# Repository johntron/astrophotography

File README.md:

# Astrophotography image processing

## Curriculum

* [Introduction to astrophotography](#introduction-to-astrophotography)
* [Image acquisition](#image-acquisition)
* [Image calibration](#image-calibration)
* [Image stacking](#image-stacking)
* [Image enhancement](#image-enhancement)
* [Color processing](#color-processing)
* [Advanced techniques](#advanced-techniques)
* [Image analysis](#image-analysis)

## Introduction to astrophotography

Learn the basics of astrophotography, including the equipment used, camera settings, and exposure times.

## Image acquisition

Learn how to capture images of the night sky using a digital camera or a telescope.

## Image calibration

Learn how to process raw astronomical images, including dark frame subtraction, flat field correction, and bias
correction.

### 1. Introduction to image calibration

Learn the importance of image calibration in astrophotography and its impact on the final image quality.

<dl>
   <dt>Bias frames</dt>
   <dd>Used to capture electronic bias inherent in sensor (zero point), so it can be removed from light frames. Does not capture or account for read noise.</dd>

   <dt>Dark frames</dt>
   <dd>Used to capture noise caused by heat generated during exposures and amplifiers (dark current), so it can be removed from light frames. Includes electronic bias, so bias frames must be subtracted from dark frames, or only dark frames should be used (no bias frames) - <em>❓ is this true❓</em></dd>

   <dt>Flat frames</dt>
   <dd>Used to capture optical imperfections in imaging path, so it can be corrected for. Can correct for minor vignette, sensor mottling (if any), as well as dust and other stray particles. Captured when all pixels are irradiated the same amount. During image processing, light frames are divided by flat frames. This effectively normalizes the range of each pixel by reducing the brightness of pixels with few optical obstructions.</dd>

   <dt>Flat dark frames</dt>
   <dd>Alternative to bias and dark frames for sensors that can't capture these types of calibration frames effectively.</dd>
</dl>

Reference:

* https://telescope.live/blog/learning-about-amp-glow#:~:text=Amplifier%20glow%20refers%20to%20a,circuitry%20of%20the%20imaging%20chip.

### 2. Capturing calibration frames

Dark and flat frames should be captured using same exposure as light frames. Dust can accumulate on the sensor during imaging, and jostling the instrument can dislodge dist. For these reasons, flat frames should be taken immediately after capturing light frames. Bias frames - if used - should be taken with minimal exposure.

### 2. Dark frame subtraction

Dark bias correction (includes sensor bias):

```python
dark_corrected_image = raw_image - reference_dark_image
```

Reference:

* https://prancer.physics.louisville.edu/astrowiki/index.php/Image_processing_with_Python_and_SciPy#Correcting_and_Combining_Images

### 3. Flat field correction

Flat field correction:

```python
final_image = dark_corrected_image / reference_flat_image
```

Reference:

* https://www.macobservatory.com/blog/2018/11/3/how-to-take-easy-flats-using-an-inexpensive-light-source
* https://prancer.physics.louisville.edu/astrowiki/index.php/Image_processing_with_Python_and_SciPy#Correcting_and_Combining_Images
* https://homepages.inf.ed.ac.uk/rbf/HIPR2/pixdiv.htm

### 4. Bias correction

This isn't necessary when using dark frames, because dark frames include electronic bias; however, if bias frames were used, the correction would use subtraction.

### 6. Image calibration techniques

Individual calibration frames can be combined to create a "master" calibration frame - e.g. master dark frame. These master frames should be combined with light frames of the same exposure.

To save time, a library of calibration frames can be created ahead of time. This avoids the time-consuming process of creating calibration frames during an imaging session. Most (all?) calibration frames can be created while the sun is up; however, accounting for temperature would be hard.

### 7. Image calibration settings

Learn how to adjust image calibration settings to produce the best final image, including choosing the right number of
images to use and the best calibration technique.

### 8. Outstanding questions

* If creating a calibration frame library, how do you account for temperature?
* How many calibration frames should be included in a master frame?

## Image stacking

Learn how to combine multiple images to increase the signal-to-noise ratio and produce a final image
with greater detail.

1. Introduction to image stacking: Learn the basics of image stacking and its importance in astrophotography.
1. Image acquisition: Learn how to capture images of the night sky using a digital camera or a telescope.
1. Image calibration: Learn how to process raw astronomical images, including dark frame subtraction, flat field
   correction, and bias correction.
1. Registration: Learn how to align and register multiple images to be stacked, including techniques for eliminating
   field rotation, field curvature, and focal plane distortion.
2. Methods: Learn about different image stacking methods, including average stacking, median stacking, and sigma
   clipping.
3. Settings: Learn how to adjust image stacking settings to produce the best final image, including choosing the
   right number of images to stack and the best stacking method.
4. Post-processing: Learn how to post-process the final stacked image using techniques such as histogram stretching,
   noise reduction, and sharpening.

## Image enhancement

Learn how to process and enhance final images using techniques such as histogram stretching, noise
reduction, and sharpening.

1. Introduction to image enhancement: Learn the importance of image enhancement in astrophotography and its impact
   on the final image quality.
2. Image processing software: Learn how to use image processing software, such as Adobe Photoshop, GIMP, or
   PixInsight, to enhance astrophotographic images.
2. Histogram stretching: Learn how to adjust the image brightness and contrast using histogram stretching to bring
   out faint details in the image.
2. Noise reduction: Learn how to reduce the noise in an image using techniques such as wavelet processing, selective
   smoothing, and median filtering.
2. Sharpening: Learn how to sharpen the details in an image using techniques such as unsharp masking, high-pass
   filtering, and deconvolution.
2. Color processing: Learn how to adjust the colors in an image to bring out the best representation of the night
   sky, including techniques for color balancing, color correction, and color grading.
2. Layer masks: Learn how to use layer masks to selectively apply image processing techniques to specific areas of
   an image.

## Color processing

Learn how to create a color image from a set of monochrome images captured through different
filters.

1. Introduction to color processing: Learn the importance of color processing in astrophotography and its impact on the
   final image quality.
1. Color theory: Learn the basics of color theory and how it applies to astrophotography.
1. Image processing software: Learn how to use image processing software, such as Adobe Photoshop, GIMP, or PixInsight,
   to process the colors in astrophotographic images.
1. Color balancing: Learn how to balance the colors in an image to achieve a natural-looking representation of the night
   sky.
1. Color correction: Learn how to correct the colors in an image to bring out the best representation of the celestial
   objects, including techniques for removing color casts, fixing white balance, and adjusting saturation.
1. Color grading: Learn how to adjust the colors in an image for artistic effect, including techniques for color grading
   and creating color-lookup tables.
1. Layer masks: Learn how to use layer masks to selectively apply color processing techniques to specific areas of an
   image.

## Advanced techniques

Learn about advanced techniques such as luminance layering, layer masks, and star tracking for
capturing sharp images of the night sky.

1. Advanced image processing techniques: Learn about advanced image processing techniques, including non-linear image
   processing, HDR imaging, and advanced color processing.
1. Advanced stacking techniques: Learn about advanced stacking techniques, including median stacking, sigma clipping,
   and multiscale processing.
1. Image restoration: Learn about techniques for restoring images, including removing artifacts, correcting distortion,
   and repairing damage.
1. Astrophotography with telescopes: Learn how to capture astrophotographic images using a telescope, including
   techniques for focusing, guiding, and stacking.
1. Astrophotography with specialized cameras: Learn how to capture astrophotographic images using specialized cameras,
   such as CCD or CMOS cameras.
1. Astrophotography with narrowband filters: Learn how to capture images using narrowband filters, including
   hydrogen-alpha, oxygen-iii, and sulfur-ii filters.
1. Image integration: Learn how to integrate multiple images captured under different conditions or with different
   equipment to produce a final image with improved quality and detail.

## Image analysis

Learn how to analyze astrophotographic images to extract scientific information, such as determining
the position and brightness of stars, the size of galaxies, and the presence of nebulae.

1. Introduction to image analysis: Learn about the importance of image analysis in astrophotography and its role in
   extracting scientific information from images.
1. Image processing software: Learn how to use image processing software, such as PixInsight or IRAF, for image
   analysis.
1. Photometry: Learn how to measure the brightness of celestial objects in an image, including techniques for aperture
   photometry, PSF photometry, and profile fitting.
1. Astrometry: Learn how to measure the positions of celestial objects in an image, including techniques for plate
   solving and world coordinate systems.
1. Image statistics: Learn how to extract information about the distribution and properties of the data in an image,
   including techniques for computing mean, median, mode, standard deviation, and skewness.
1. Image visualization: Learn how to visualize the data in an image, including techniques for creating histograms,
   contour plots, and surface plots.
1. Object detection: Learn how to detect celestial objects in an image, including techniques for source extraction,
   deblending, and false detection removal.

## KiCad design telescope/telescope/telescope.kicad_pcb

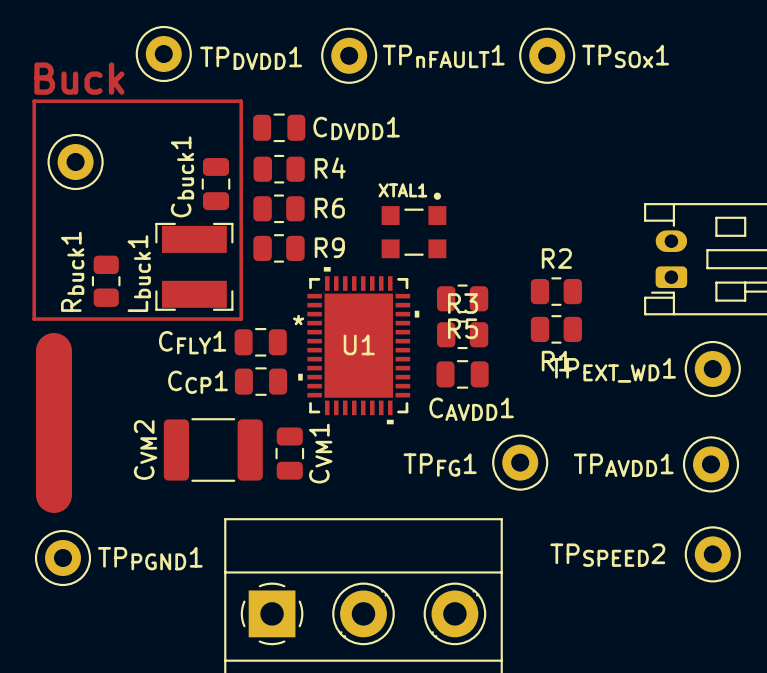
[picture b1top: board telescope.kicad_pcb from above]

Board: 2 copper layers, 30 parts (0 on the bottom side), 25 nets, no tracks yet.

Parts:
C_{AVDD}1: 1uF; C_0805_2012Metric
C_{CP}1: 1uF; C_0805_2012Metric
C_{DVDD}1: 1uF; C_0805_2012Metric
C_{FLY}1: 47nF; C_0805_2012Metric
C_{VM}1: 100nF; C_0805_2012Metric
C_{VM}2: 100uF; C_1812_4532Metric
C_{buck}1: 10V 22uF; C_0805_2012Metric
J1: Conn_01x03; TerminalBlock_Phoenix_MKDS-1,5-3-5.08_1x03_P5.08mm_Horizont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
J2: STEMMA QT; JST_PH_S2B-PH-K_1x02_P2.00mm_Horizontal
L_{buck}1: 47uH; L_Bourns-SRN4018
NT1: NetTie_3; NetTie-3_SMD_Pad2.0mm
R1, R2, R3, R4, R5: 5R1; R_0805_2012Metric
R6, R9: 10K; R_0805_2012Metric
R_{buck}1: 22R; R_0805_2012Metric
TP_{AVDD}1: 5000; TestPoint_Loop_D1.80mm_Drill1.0mm_Beaded
TP_{BUCK}1: TestPoint; TestPoint_Loop_D1.80mm_Drill1.0mm_Beaded
TP_{DVDD}1: 5000; TestPoint_Loop_D1.80mm_Drill1.0mm_Beaded
TP_{EXT_WD}1: 5000; TestPoint_Loop_D1.80mm_Drill1.0mm_Beaded
TP_{FG}1: 5000; TestPoint_Loop_D1.80mm_Drill1.0mm_Beaded
TP_{PGND}1: 5000; TestPoint_Loop_D1.80mm_Drill1.0mm_Beaded
TP_{SOx}1: 5000; TestPoint_Loop_D1.80mm_Drill1.0mm_Beaded
TP_{SPEED}2: 5000; TestPoint_Loop_D1.80mm_Drill1.0mm_Beaded
TP_{nFAULT}1: 5000; TestPoint_Loop_D1.80mm_Drill1.0mm_Beaded
U1: PMCF8316A1VRGFR; QFN_A1VRGFR_TEX
XTAL1: ECS-327TXO-30-TR; OSC_ECS-327TXO-30-TR

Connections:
/AV_{DD}: C_{AVDD}1.2, R1.1, R2.1, R3.1, R4.1, R5.1, R9.1, TP_{AVDD}1.1, U1.27 (AVDD), XTAL1.1 (OE), XTAL1.4 (SUPPLY_VOLTAGE)
/Buck/FB_{buck}: C_{buck}1.1, L_{buck}1.2, R_{buck}1.2, TP_{BUCK}1.1, U1.3 (FB_BK)
/Buck/GND_{buck}: C_{buck}1.2, U1.4 (GND_BK)
/Buck/SW_{buck}: L_{buck}1.1, R_{buck}1.1, U1.5 (SW_BK)
/TCXO/CLKOUT: U1.33 (EXT_CLK), XTAL1.3 (OUTPUT)
GNDA: C_{DVDD}1.1, C_{VM}1.2, C_{VM}2.2, NT1.2
unnamed: J1.1, U1.13 (OUT_A), U1.14 (OUT_A)
unnamed: J1.2, U1.16 (OUT_B), U1.17 (OUT_B)
unnamed: J1.3, U1.19 (OUT_C), U1.20 (OUT_C)
unnamed: J2.1, R1.2, U1.31 (SCL)
unnamed: J2.2, R2.2, U1.30 (SDA)
unnamed: NT1.1, TP_{PGND}1.1
unnamed: R6.2, U1.35 (BRAKE)
unnamed: C_{CP}1.1, U1.8 (CP)
unnamed: C_{FLY}1.2, U1.7 (CPH)
unnamed: C_{FLY}1.1, U1.6 (CPL)
unnamed: R9.2, U1.34 (DIR)
unnamed: C_{DVDD}1.2, TP_{DVDD}1.1, U1.1 (DVDD)
unnamed: TP_{EXT_WD}1.1, U1.32 (EXT_WD)
unnamed: R5.2, TP_{FG}1.1, U1.29 (FG)
unnamed: U1.12 (PGND), U1.15 (PGND)
unnamed: R4.2, TP_{SOx}1.1, U1.38 (SOX)
unnamed: TP_{SPEED}2.1, U1.28 (SPEED/WAKE)
unnamed: R3.2, TP_{nFAULT}1.1, U1.40 (nFAULT)
VCC: C_{CP}1.2, C_{VM}1.1, C_{VM}2.1, U1.9 (VM), U1.10 (VM), U1.11 (VM)

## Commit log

2023-02-06 more
2023-02-06 uses samples from https://www.astropix.com/html/processing/practice_files.html
2023-02-06 curriculum
2023-02-06 notes
2023-02-13 analysis
2023-02-15 crawler before moving to storage
2023-02-17 refactoring
2023-02-17 data analysis
2023-02-17 moves shopping modules to new folder
2023-02-17 removes old input files
2023-02-17 cleanup
2023-02-17 jetbrains workspace
2023-02-17 image processing
2023-02-17 checkpoint
2023-02-25 clustering of features
2023-10-02 motor controller circuit
2023-12-11 Checkpoint for Pi Cam vision controller using Rust
2023-12-11 Checkpoint for BLDC tracking mount controller
2023-12-11 Add devcontainer.json and gphoto.sh scripts
2023-12-11 Add sourcegraph.cody-ai extension to devcontainer.json
2023-12-11 Update gphoto.sh script to include installation and configuration steps for libgphoto2 and gphoto2
